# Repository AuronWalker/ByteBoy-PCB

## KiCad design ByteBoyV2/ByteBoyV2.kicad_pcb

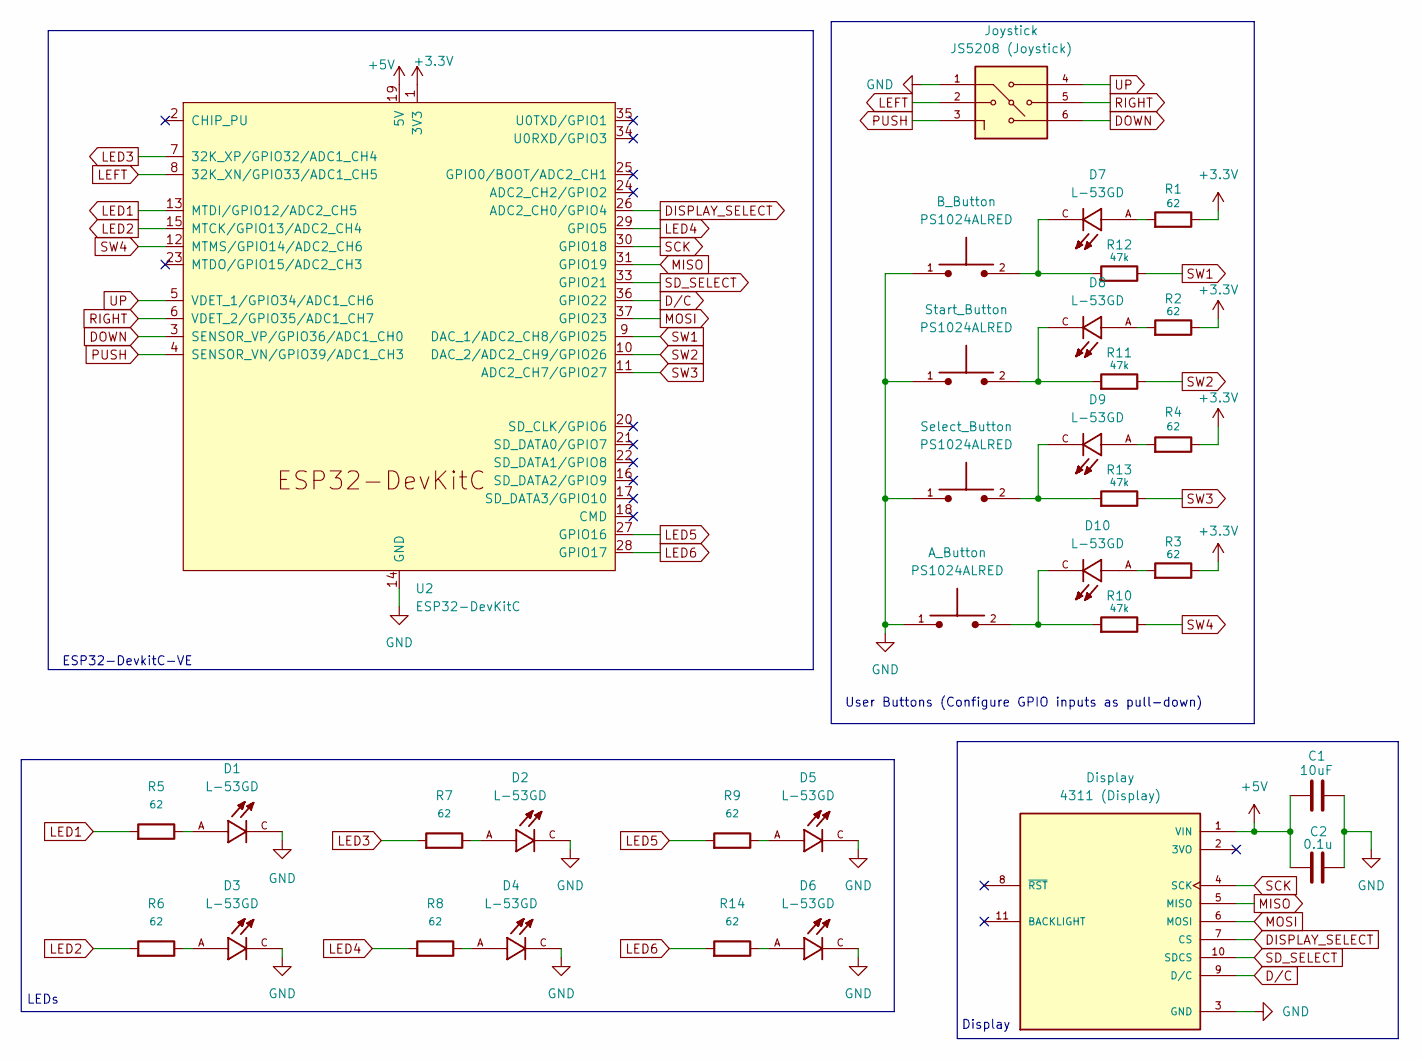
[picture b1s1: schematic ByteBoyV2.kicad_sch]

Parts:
A_Button: PS1024ALRED; SW_PS1024ALRED; PARTREV C
B_Button: PS1024ALRED; SW_PS1024ALRED; PARTREV C
C1: 10uF; C_Rect_L7.0mm_W2.5mm_P5.00mm
C2: 0.1u; C_Rect_L7.0mm_W2.5mm_P5.00mm
D1, D2, D3, D4, D5, D6, D7, D8, D9, D10: L-53GD; LEDRD254W50D500H1060; PARTREV V.3
Display: 4311 (Display); MODULE_4311; PARTREV 2023-07-05
Joystick: JS5208 (Joystick); SW_JS5208; PARTREV D; DigiKey_Part_Number EG4561-ND
R1, R2, R3, R4, R5, R6, R7, R8, R9, R14: 62; R_Axial_DIN0207_L6.3mm_D2.5mm_P7.62mm_Horizontal
R10, R11, R12, R13: 47k; R_Axial_DIN0207_L6.3mm_D2.5mm_P7.62mm_Horizontal
Select_Button: PS1024ALRED; SW_PS1024ALRED; PARTREV C
Start_Button: PS1024ALRED; SW_PS1024ALRED; PARTREV C
U2: ESP32-DevKitC

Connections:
+3.3V: R1.2, R2.2, R3.2, R4.2, U2.1 (3V3)
+5V: C1.1, C2.1, Display.1 (VIN), U2.19 (5V)
DISPLAY_SELECT: Display.7 (CS), U2.26 (ADC2_CH0/GPIO4)
DOWN: Joystick.6, U2.3 (SENSOR_VP/GPIO36/ADC1_CH0)
D/C: Display.9 (D/C), U2.36 (GPIO22)
GND: A_Button.1, B_Button.1, C1.2, C2.2, D1.C, D2.C, D3.C, D4.C, D5.C, D6.C, Display.3 (GND), Joystick.1, Select_Button.1, Start_Button.1, U2.14 (GND), U2.32 (GND), U2.38 (GND)
LED1: R5.1, U2.13 (MTDI/GPIO12/ADC2_CH5)
LED2: R6.1, U2.15 (MTCK/GPIO13/ADC2_CH4)
LED3: R7.1, U2.7 (32K_XP/GPIO32/ADC1_CH4)
LED4: R8.1, U2.29 (GPIO5)
LED5: R9.1, U2.27 (GPIO16)
LED6: R14.1, U2.28 (GPIO17)
LEFT: Joystick.2, U2.8 (32K_XN/GPIO33/ADC1_CH5)
MISO: Display.5 (MISO), U2.31 (GPIO19)
MOSI: Display.6 (MOSI), U2.37 (GPIO23)
unnamed: D1.A, R5.2
unnamed: D2.A, R7.2
unnamed: D3.A, R6.2
unnamed: D4.A, R8.2
unnamed: D5.A, R9.2
unnamed: D6.A, R14.2
unnamed: D7.A, R1.1
unnamed: B_Button.2, D7.C, R12.1
unnamed: D8.A, R2.1
unnamed: D8.C, R11.1, Start_Button.2
unnamed: D9.A, R4.1
unnamed: D9.C, R13.1, Select_Button.2
unnamed: D10.A, R3.1
unnamed: A_Button.2, D10.C, R10.1
PUSH: Joystick.3, U2.4 (SENSOR_VN/GPIO39/ADC1_CH3)
RIGHT: Joystick.5, U2.6 (VDET_2/GPIO35/ADC1_CH7)
SCK: Display.4 (SCK), U2.30 (GPIO18)
SD_SELECT: Display.10 (SDCS), U2.33 (GPIO21)
SW1: R12.2, U2.9 (DAC_1/ADC2_CH8/GPIO25)
SW2: R11.2, U2.10 (DAC_2/ADC2_CH9/GPIO26)
SW3: R13.2, U2.11 (ADC2_CH7/GPIO27)
SW4: R10.2, U2.12 (MTMS/GPIO14/ADC2_CH6)
UP: Joystick.4, U2.5 (VDET_1/GPIO34/ADC1_CH6)

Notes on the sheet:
LEDs
User Buttons (Configure GPIO inputs as pull-down)
ESP32-DevkitC-VE
Display

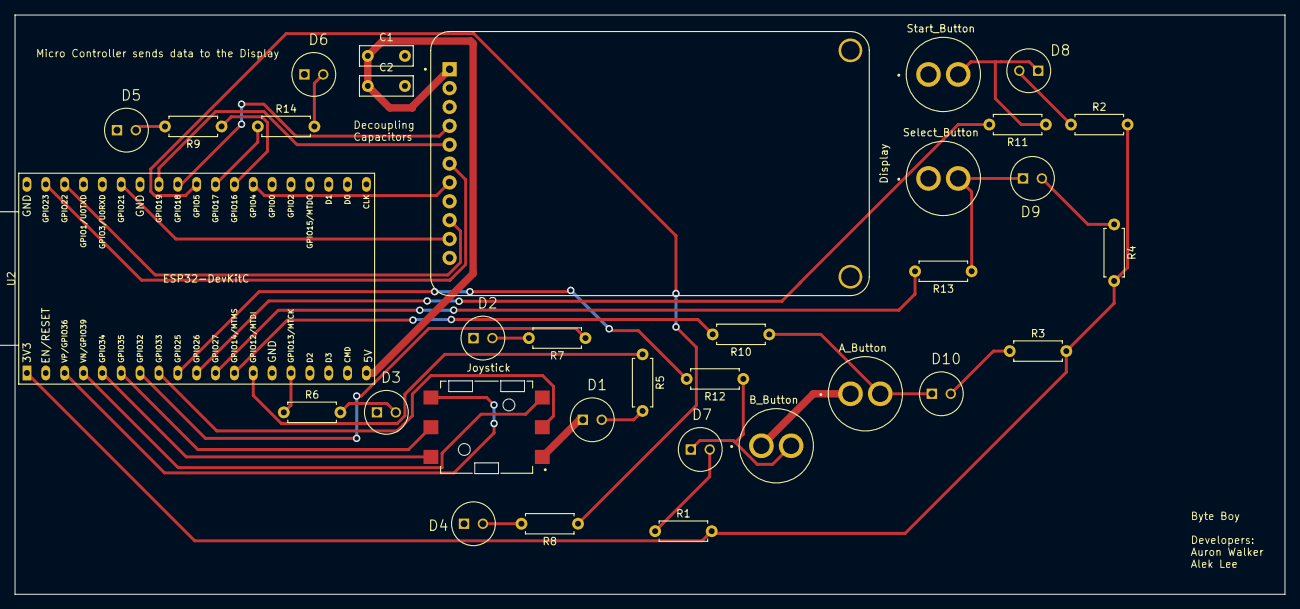
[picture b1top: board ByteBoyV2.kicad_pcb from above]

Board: 2 copper layers, 171.0 x 78.0 mm, 33 parts (0 on the bottom side), 38 nets.

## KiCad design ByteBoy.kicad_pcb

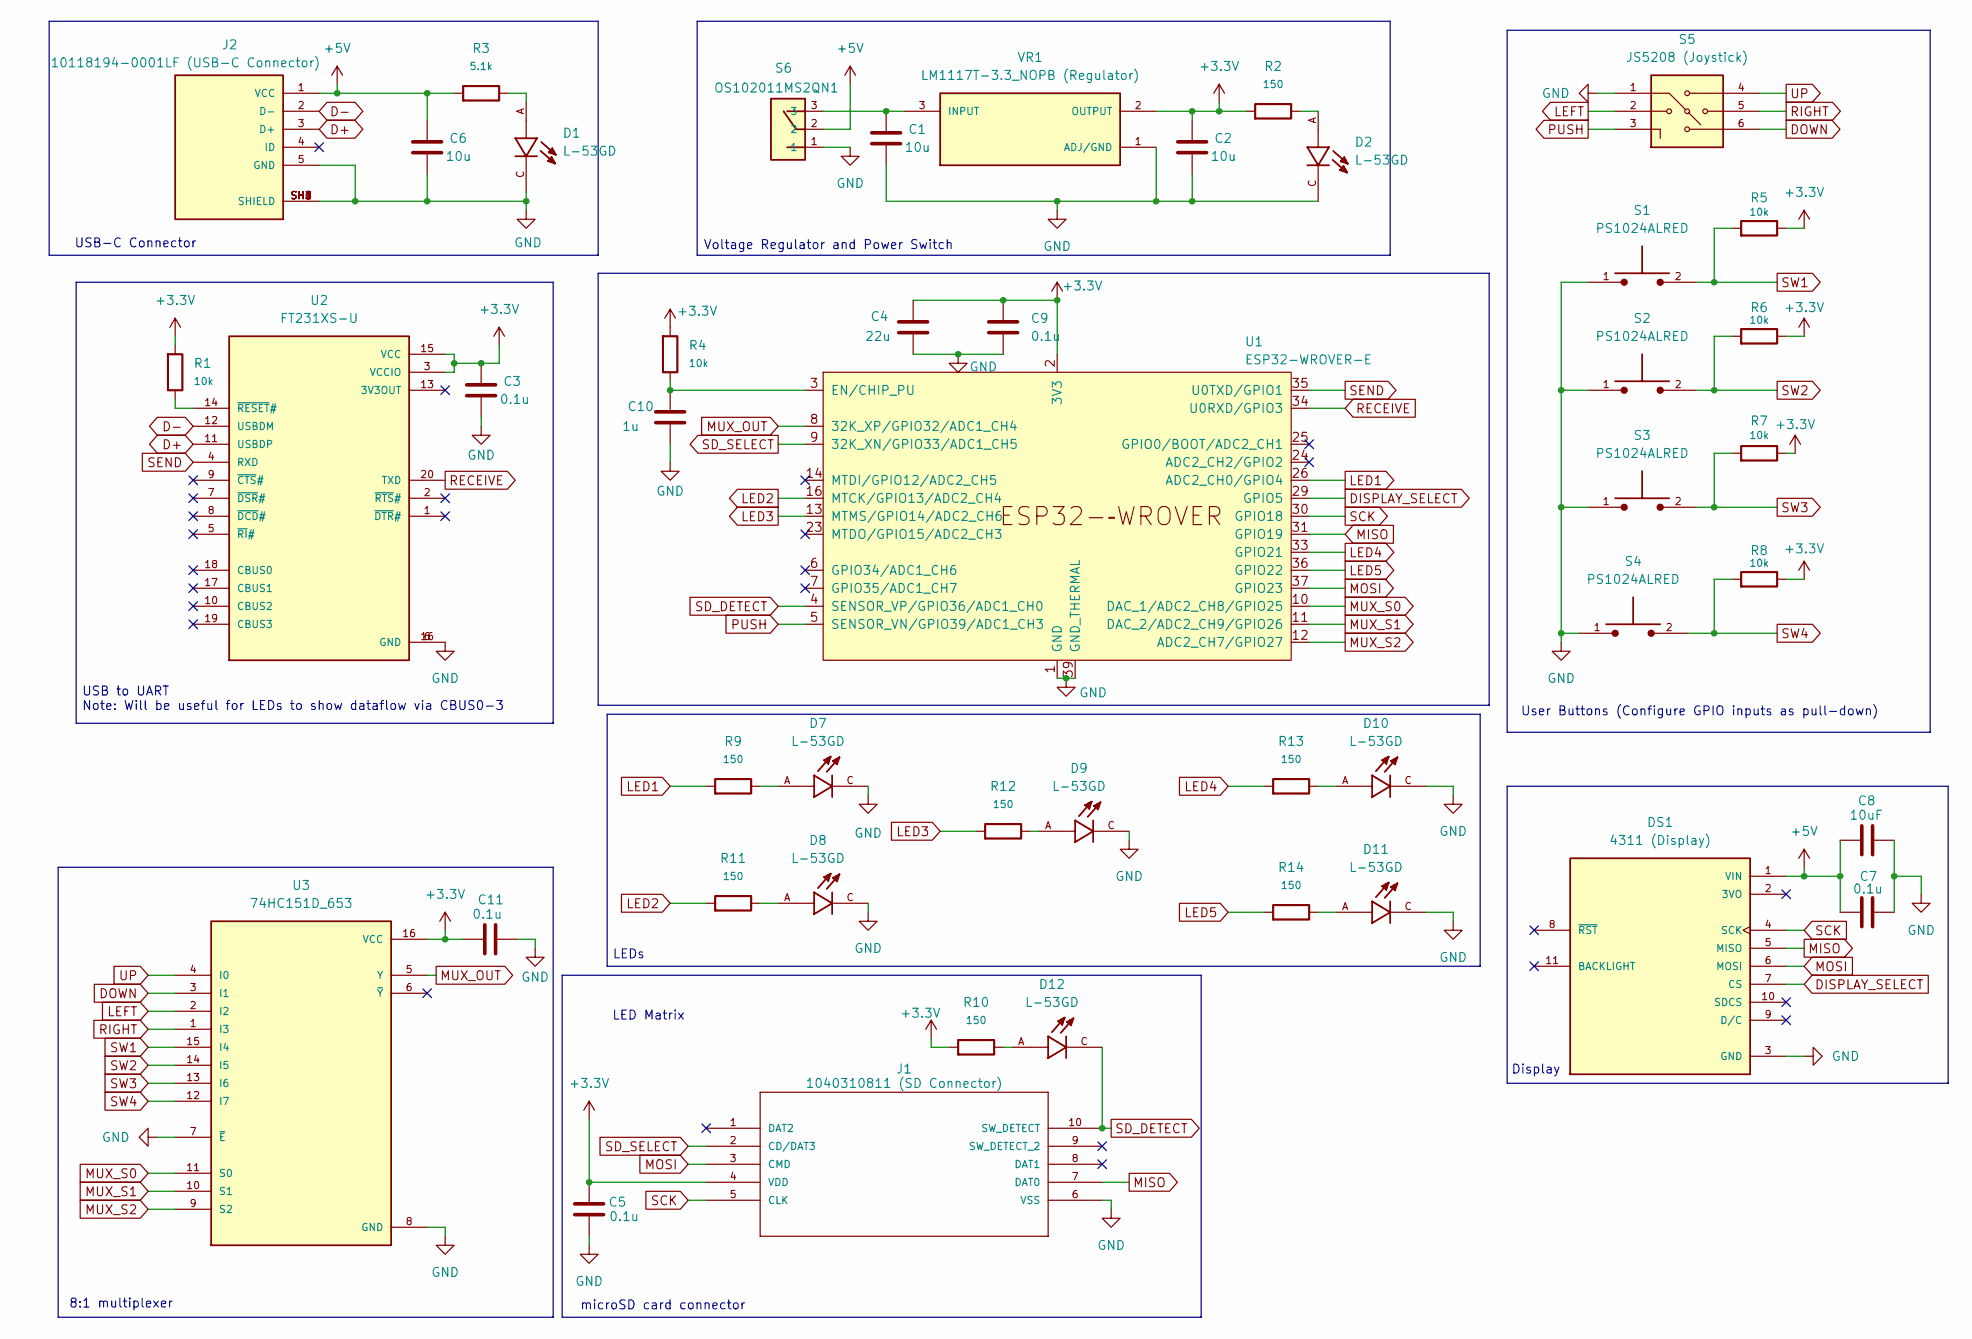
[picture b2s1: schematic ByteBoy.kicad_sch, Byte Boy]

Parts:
C1, C2, C6: 10u; C_Rect_L7.0mm_W2.5mm_P5.00mm
C3, C5, C7, C9, C11: 0.1u; C_Rect_L7.0mm_W2.5mm_P5.00mm
C4: 22u; C_Rect_L7.0mm_W2.5mm_P5.00mm
C8: 10uF; C_Rect_L7.0mm_W2.5mm_P5.00mm
C10: 1u; C_Rect_L7.0mm_W2.5mm_P5.00mm
D1, D2, D7, D8, D9, D10, D11, D12: L-53GD; LEDRD254W50D500H1060; PARTREV V.3
DS1: 4311 (Display); MODULE_4311; PARTREV 2023-07-05
J1: 1040310811 (SD Connector); 104031-0811_MOL; MANUFACTURER_PART_NUMBER 1040310811
J2: 10118194-0001LF (USB-C Connector); AMPHENOL_10118194-0001LF; PARTREV D
R1, R4, R5, R6, R7, R8: 10k; R_Axial_DIN0207_L6.3mm_D2.5mm_P7.62mm_Horizontal
R2, R9, R10, R11, R12, R13, R14: 150; R_Axial_DIN0207_L6.3mm_D2.5mm_P7.62mm_Horizontal
R3: 5.1k; R_Axial_DIN0207_L6.3mm_D2.5mm_P7.62mm_Horizontal
S1, S2, S3, S4: PS1024ALRED; SW_PS1024ALRED; PARTREV C
S5: JS5208 (Joystick); SW_JS5208; PARTREV D; DigiKey_Part_Number EG4561-ND
S6: OS102011MS2QN1; SW_OS102011MS2QN1
U1: ESP32-WROVER-E
U2: FT231XS-U; SOP63P600X175-20N; PARTREV 1.2
U3: 74HC151D_653; SOIC127P600X175-16N; PARTREV 6; DigiKey_Part_Number 1727-7294-1-ND
VR1: LM1117T-3.3_NOPB (Regulator); TO254P1054X470X1955-3; PARTREV O; DigiKey_Part_Number LM1117T-3.3/NOPB-ND

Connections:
+3.3V: C2.2, C3.2, C4.1, C5.1, C9.1, C11.2, J1.4 (VDD), R1.1, R2.1, R4.1, R5.2, R6.2, R7.2, R8.2, R10.1, U1.2 (3V3), U2.3 (VCCIO), U2.15 (VCC), U3.16 (VCC), VR1.2 (OUTPUT)
+5V: C6.2, C7.1, C8.1, DS1.1 (VIN), J2.1 (VCC), R3.1, S6.2
D+: J2.3 (D+), U2.11 (USBDP)
D-: J2.2 (D-), U2.12 (USBDM)
DISPLAY_SELECT: DS1.7 (CS), U1.29 (GPIO5)
DOWN: S5.6, U3.3 (I1)
GND: C1.1, C2.1, C3.1, C4.2, C5.2, C6.1, C7.2, C8.2, C9.2, C10.2, C11.1, D1.C, D2.C, D7.C, D8.C, D9.C, D10.C, D11.C, DS1.3 (GND), J1.6 (VSS), J2.5 (GND), J2.SH1 (SHIELD), J2.SH2 (SHIELD), J2.SH3 (SHIELD), J2.SH4 (SHIELD), J2.SH5 (SHIELD), J2.SH6 (SHIELD), S1.1, S2.1, S3.1, S4.1, S5.1, S6.1, U1.1 (GND), U1.15 (GND), U1.38 (GND), U1.39 (GND_THERMAL), U2.6 (GND), U2.16 (GND), U3.7 (~E), U3.8 (GND), VR1.1 (ADJ/GND)
LED1: R9.1, U1.26 (ADC2_CH0/GPIO4)
LED2: R11.1, U1.16 (MTCK/GPIO13/ADC2_CH4)
LED3: R12.1, U1.13 (MTMS/GPIO14/ADC2_CH6)
LED4: R13.1, U1.33 (GPIO21)
LED5: R14.1, U1.36 (GPIO22)
LEFT: S5.2, U3.2 (I2)
MISO: DS1.5 (MISO), J1.7 (DAT0), U1.31 (GPIO19)
MOSI: DS1.6 (MOSI), J1.3 (CMD), U1.37 (GPIO23)
MUX_OUT: U1.8 (32K_XP/GPIO32/ADC1_CH4), U3.5 (Y)
MUX_S0: U1.10 (DAC_1/ADC2_CH8/GPIO25), U3.11 (S0)
MUX_S1: U1.11 (DAC_2/ADC2_CH9/GPIO26), U3.10 (S1)
MUX_S2: U1.12 (ADC2_CH7/GPIO27), U3.9 (S2)
unnamed: D1.A, R3.2
unnamed: D2.A, R2.2
unnamed: D7.A, R9.2
unnamed: D8.A, R11.2
unnamed: D9.A, R12.2
unnamed: D10.A, R13.2
unnamed: D11.A, R14.2
unnamed: D12.A, R10.2
unnamed: C10.1, R4.2, U1.3 (EN/CHIP_PU)
unnamed: R1.2, U2.14 (~RESET#)
unnamed: C1.2, S6.3, VR1.3 (INPUT)
PUSH: S5.3, U1.5 (SENSOR_VN/GPIO39/ADC1_CH3)
RECEIVE: U1.34 (U0RXD/GPIO3), U2.20 (TXD)
RIGHT: S5.5, U3.1 (I3)
SCK: DS1.4 (SCK), J1.5 (CLK), U1.30 (GPIO18)
SD_DETECT: D12.C, J1.10 (SW_DETECT), U1.4 (SENSOR_VP/GPIO36/ADC1_CH0)
SD_SELECT: J1.2 (CD/DAT3), U1.9 (32K_XN/GPIO33/ADC1_CH5)
SEND: U1.35 (U0TXD/GPIO1), U2.4 (RXD)
SW1: R5.1, S1.2, U3.15 (I4)
SW2: R6.1, S2.2, U3.14 (I5)
SW3: R7.1, S3.2, U3.13 (I6)
SW4: R8.1, S4.2, U3.12 (I7)
UP: S5.4, U3.4 (I0)

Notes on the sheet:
LEDs
USB-C Connector
microSD card connector
User Buttons (Configure GPIO inputs as pull-down)
USB to UART Note: Will be useful for LEDs to show dataflow via CBUS0-3
LED Matrix
Voltage Regulator and Power Switch
Display
8:1 multiplexer

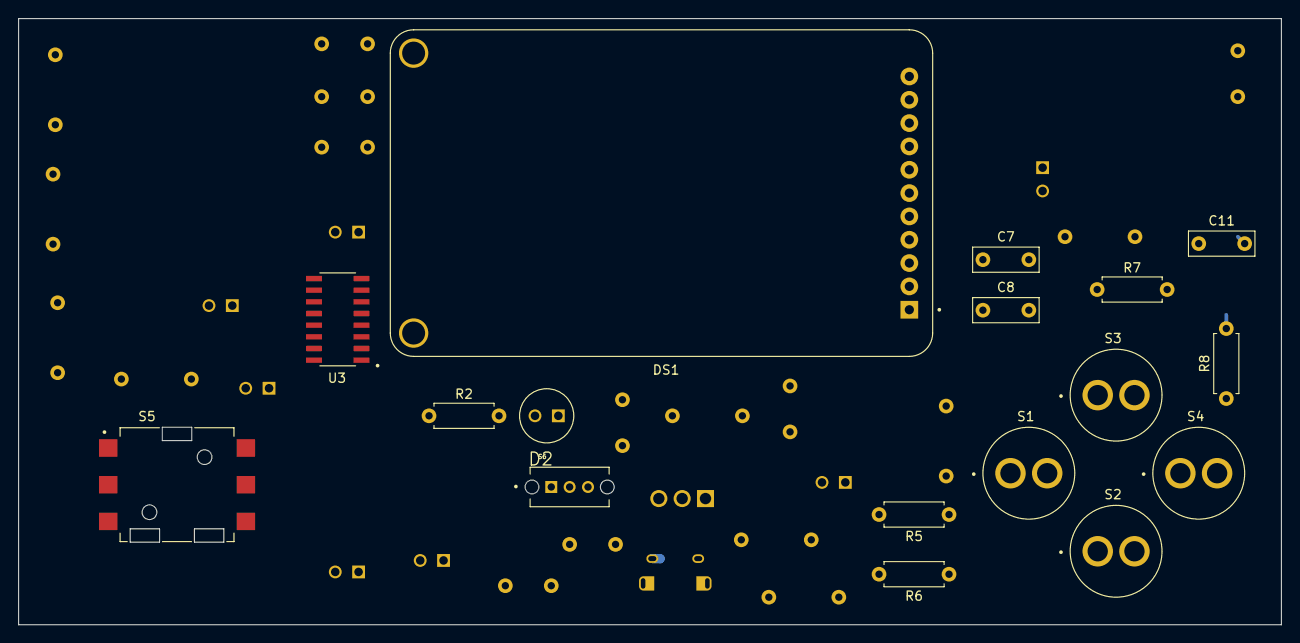
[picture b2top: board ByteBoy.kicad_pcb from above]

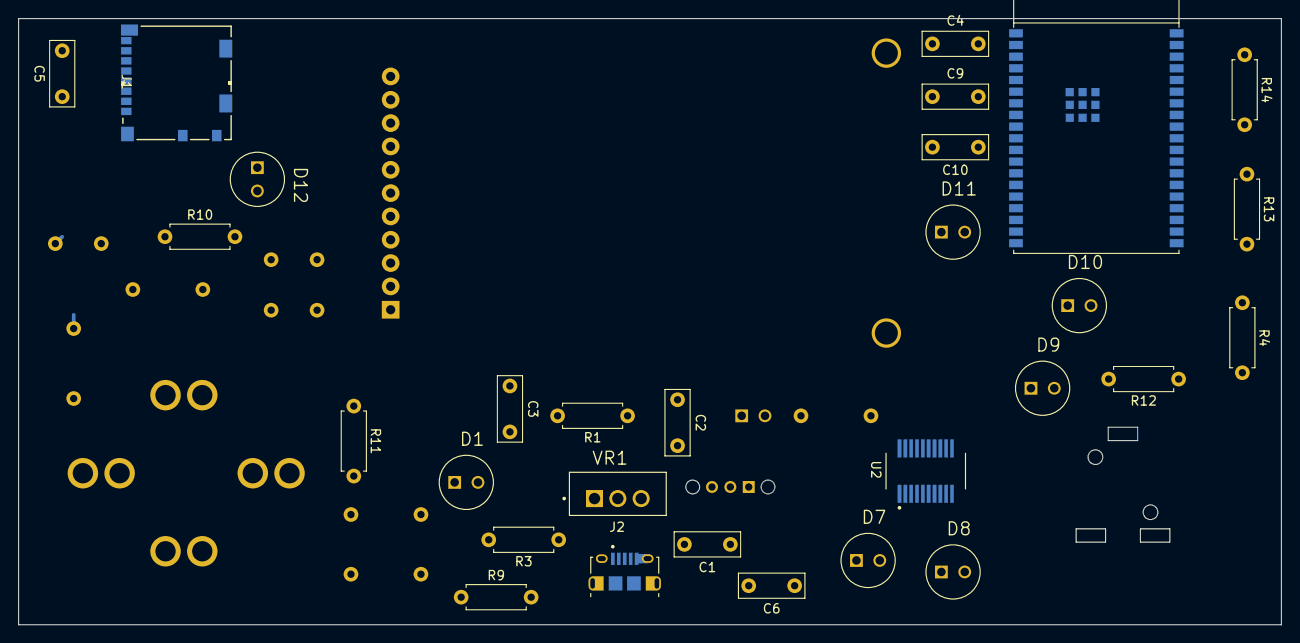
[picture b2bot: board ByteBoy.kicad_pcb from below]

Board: 2 copper layers, 137.5 x 66.0 mm, 46 parts (29 on the bottom side), 42 nets.

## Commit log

2025-08-07 Footprints added
2025-08-10 Add .gitignore, removed KiCad artifacts
2025-08-13 added usb to uart
2025-08-14 adding decoupling
2025-08-14 schematic done :)
2025-08-17 pcb layout
2025-08-25 Changed nearly all the parts for simplicity
